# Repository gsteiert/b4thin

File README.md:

# b4thin
Beeping Blinking Business-card Badge, Thin Edition

Part of the [Beeping, Blinking Businsess-card Badge (B4) project on Hackaday](https://hackaday.io/project/177897-beeping-blinking-business-card-badge-b4)

This is a 1mm thick full-size, standard business card that can blink and beep.

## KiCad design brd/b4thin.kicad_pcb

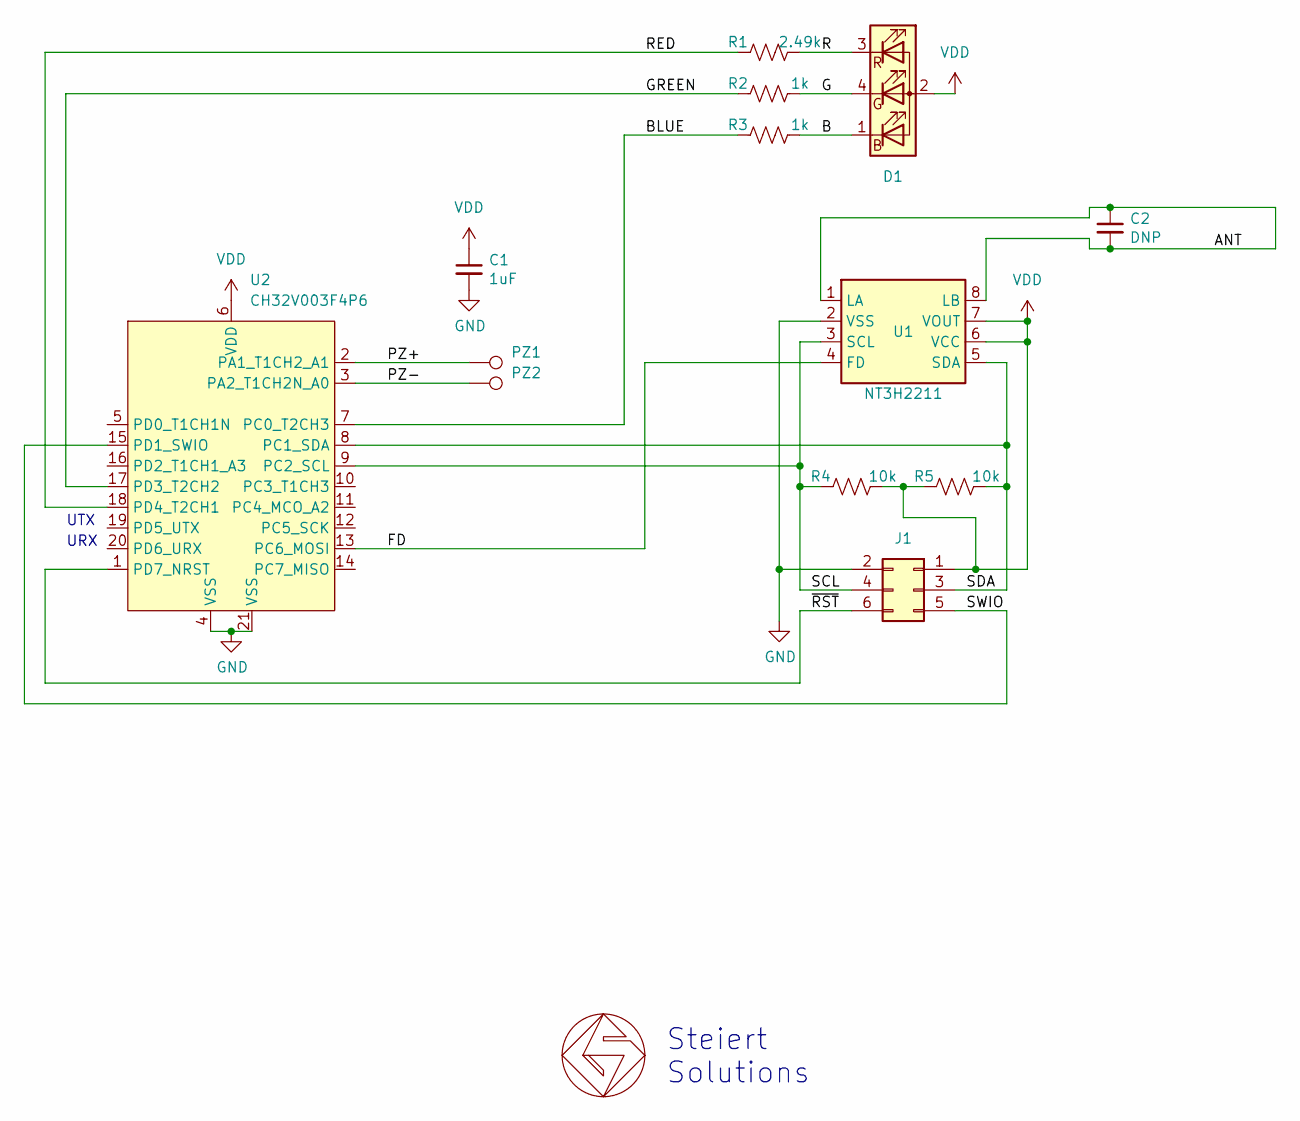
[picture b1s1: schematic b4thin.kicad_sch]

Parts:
C1: 1uF; C_0402_1005Metric; MPN CL05A105KP5NNNC; LCSC C14445
C2: DNP; C_0402_1005Metric
D1: LED_RAGB; LED_Kingbright_APFA2507_2.5x1mm_Horizontal; MPN APFA2507LQBDSEEZGKC; LCSC C5126857
GS1: GS_logo; gs_logo_200mil
J1: Conn_02x03_Odd_Even; PinHeader_2x03_P2.54mm_Vertical
PZ1, PZ2: TestPoint; TestPoint_THTPad_D2.0mm_Drill1.0mm
R1: 2.49k; R_0402_1005Metric; MPN RC0402FR-072K49L; LCSC C145071
R2, R3: 1k; R_0402_1005Metric; MPN RC0402FR-071KL; LCSC C106235
R4, R5: 10k; R_0402_1005Metric; MPN RC0402FR-0710KL; LCSC C60490
U1: NT3H2211; XQFN8_1.6x1.6mm_SOT902-3; MPN NT3H2211W0FHKH; LCSC C2905792
U2: CH32V003F4P6; QFN-20-1EP_3x3mm_P0.4mm_EP1.65x1.65mm; MPN CH32V003F4U6; LCSC C5299908

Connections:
/ANT: C2.1, C2.2, U1.1 (LA), U1.8 (LB)
/B: D1.1 (BK), R3.1
/BLUE: R3.2, U2.7 (PC0_T2CH3)
/FD: U1.4 (FD), U2.13 (PC6_MOSI)
/G: D1.4 (GK), R2.1
/GREEN: R2.2, U2.17 (PD3_T2CH2)
/PZ+: PZ1.1, U2.2 (PA1_T1CH2_A1)
/PZ-: PZ2.1, U2.3 (PA2_T1CH2N_A0)
/R: D1.3 (RK), R1.1
/RED: R1.2, U2.18 (PD4_T2CH1)
/SCL: J1.4, R4.2, U1.3 (SCL), U2.9 (PC2_SCL)
/SDA: J1.3, R5.1, U1.5 (SDA), U2.8 (PC1_SDA)
/SWIO: J1.5, U2.15 (PD1_SWIO)
/~RST: J1.6, U2.1 (PD7_NRST)
GND: C1.2, J1.2, U1.2 (VSS), U2.4 (VSS), U2.21 (VSS)
VDD: C1.1, D1.2 (A), J1.1, R4.1, R5.2, U1.6 (VCC), U1.7 (VOUT), U2.6 (VDD)

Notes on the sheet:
Steiert Solutions
UTX
URX

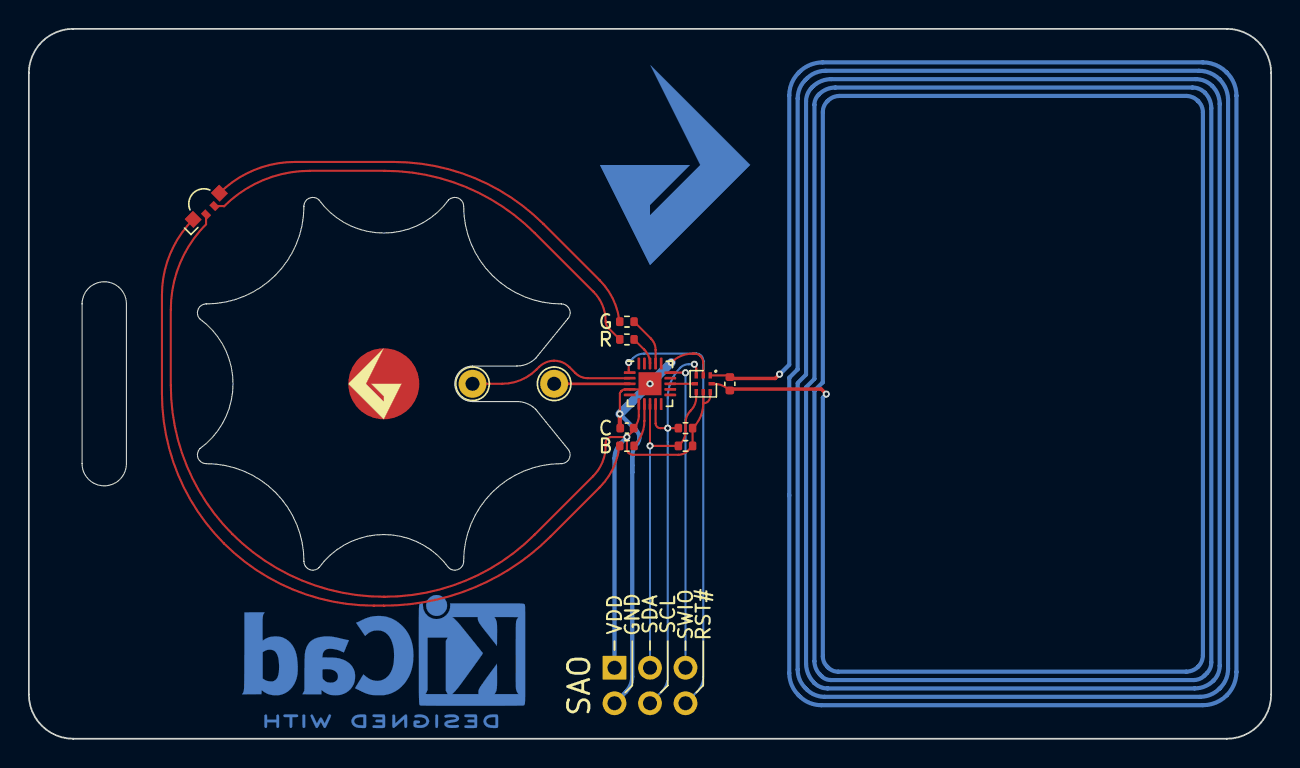
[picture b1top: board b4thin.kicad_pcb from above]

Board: 2 copper layers, 88.9 x 50.8 mm, 14 parts (1 on the bottom side), 16 nets.

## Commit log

2024-06-25 Checking in the 1mm audio/visual business card
